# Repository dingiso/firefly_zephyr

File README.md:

# Firefly

# Software prerequisites
* Zephyr RTOS 3.4.0. See [Getting Started](https://docs.zephyrproject.org/latest/getting_started/index.html).
  When doing `west init`, use `west init zephyrproject --mr v3.4.0` to install this specific version.
  Make sure you can build some of Zephyr examples before proceeding.
* IDE: At the moment, Visual Studio Code with the bunch of plugins is used (VSCode will automatically ask to install them when
  opening this repository. Other IDEs can be also potentially used, more investigation is needed. Most of the commands are run
  from the command line anyway.
* Linux or running via WSL under Windows is recommended, as Black Magic Probe programming [doesn't work on Windows](https://github.com/zephyrproject-rtos/zephyr/issues/50789)
  When running under WSL, [usbipd](https://devblogs.microsoft.com/commandline/connecting-usb-devices-to-wsl/) can be used to allow interaction
  with the hardware from WSL.

# Hardware prerequisites
* For flashing, one of [nRF devkits](https://www.nordicsemi.com/Software-and-Tools/Development-Kits) is required.

# Building and flashing
To build of the images, mentioned below, use
```bash
west build <subfolder> --pristine
```
(`--pristine` can be omitted if previous build used same subfolder, it basically means "clean, non-incremental build")

To flash it, use
```bash
west flash
```

# Contents

This repo contains sources to build following firmware images:

## Firefly
This is the "main" image, located in the `firefly` folder.
Behaviours:
* Radio: will continously listen for the radio packets (see packet structure [here](common/magic_path_packet.h)).
  This is compatible with Locket firmware from [this branch](https://github.com/aeremin/Locket_fw/tree/7Colors) and
  with the Activator firmware described below. LED color will change according to packets received.
* Bluetooth: presents itself as connectable BLE device. Provides 2 BLE services:
  * Standard battery service, containing battery level (0-100) characteristic.
  * Custom service (UUID `8ec87060-8865-4eca-82e0-2ea8e45e8221`) exposing following characteristics:
    * "Beep" (UUID `8ec87062-8865-4eca-82e0-2ea8e45e8221`). Write-only characteristic, writing a byte to it will trigger short beep,
      byte written controls the volume.
    * "Blink" (UUID `8ec87063-8865-4eca-82e0-2ea8e45e8221`). Write-only characteristic, writing anything will trigger short series
      of blinks.

  Both of the services can be used by [dedicated Android app](https://install.appcenter.ms/users/a.eremin.msu/apps/ostranna-configurator/distribution_groups/public).
  App sources are [here](https://github.com/aeremin/ostranna_configurator).
* Battery measurement. Will continously monitor battery voltage and
  * Report it via bluetooth - see above.
  * Will disable radio and LED (will keep Bluetooth enabled) if battery level is low.

## Activator
This image can be used to trigger Firefly one or to provide some settings for it.
Behaviours:
* Radio: will continously transmit radio packets (see packet structure [here](common/magic_path_packet.h)).
* LED: will have a color corresponding to foreground color of packet being transmitted.
* Bluetooth: presents itself as connectable BLE device. Provides 2 BLE services:
  * Standard battery service, containing battery level (0-100) characteristic.
  * Custom service (UUID `8ec87060-8865-4eca-82e0-2ea8e45e8221`) exposing readable and writable characteristics corresponding to the
    fields of radio packet being transmitted. This allows to control the packet from e.g. phone.

  Both of the services can be used by [dedicated Android app](https://install.appcenter.ms/users/a.eremin.msu/apps/ostranna-configurator/distribution_groups/public).
  App sources are [here](https://github.com/aeremin/ostranna_configurator).

## Smoke test
This is a test image. Currently it only contains very basic test covering SPI usage and smooth LED transitions.
Will output the test log to the UART/RTT.

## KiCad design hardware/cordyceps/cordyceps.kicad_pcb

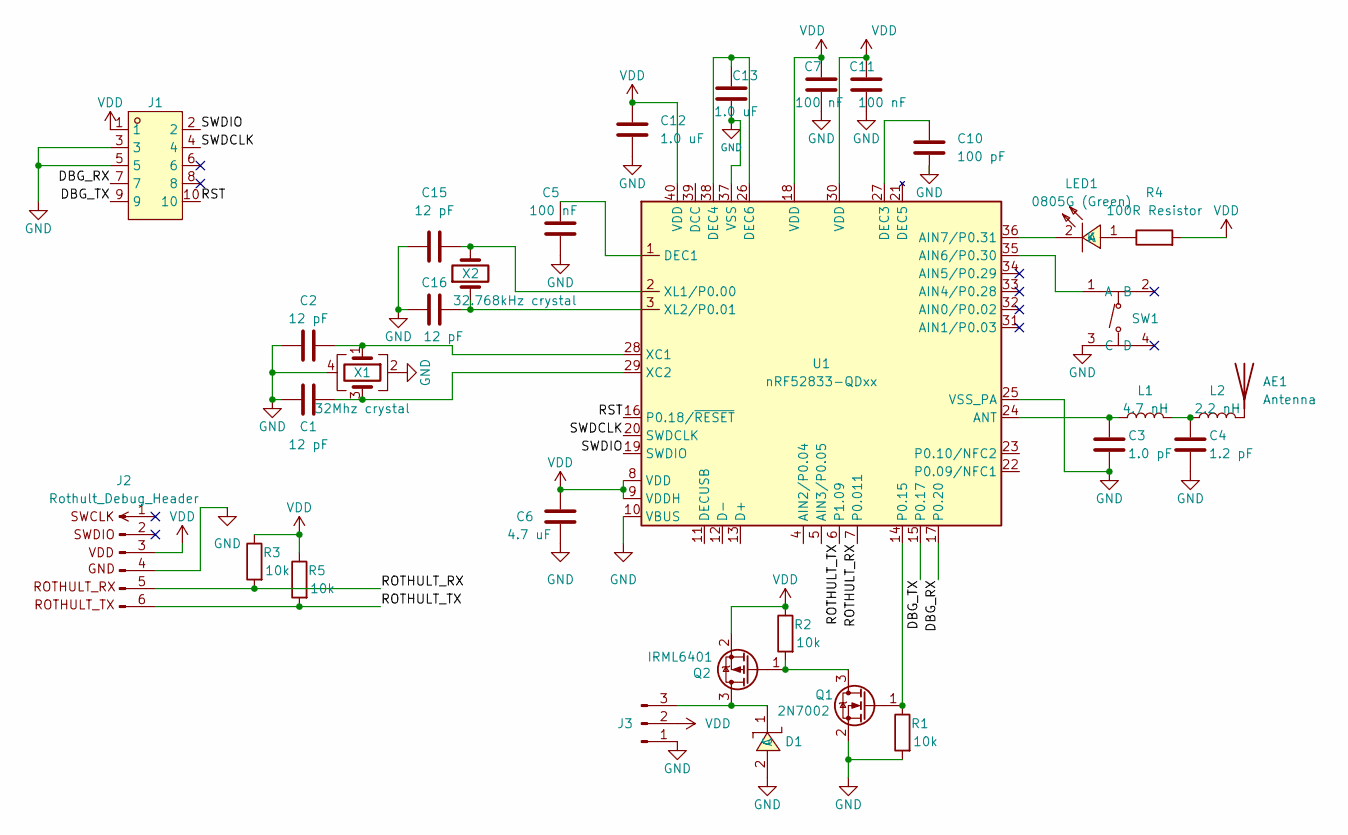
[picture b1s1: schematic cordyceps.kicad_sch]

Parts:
AE1: Antenna; Texas_SWRA117D_2.4GHz_Right
C1, C2, C15, C16: 12 pF; C_0402_1005Metric; LCSC C1547
C3: 1.0 pF; C_0402_1005Metric; LCSC C1550
C4: 1.2 pF; C_0603_1608Metric; LCSC C913539
C5, C7, C11: 100 nF; C_0402_1005Metric; LCSC C1525
C6: 4.7 uF; C_0603_1608Metric; LCSC C19666
C10: 100 pF; C_0402_1005Metric; LCSC C1546
C12, C13: 1.0 uF; C_0603_1608Metric; LCSC C15849
D1: 1N5819WS; SOD-323_L1.8-W1.3-LS2.5-RD; LCSC Part C191023
J1: KH-1.27PH180-2X5P-L7.2-SMT; HDR-SMD_10P-P1.27-V-M-R2-C5-LS5.5; LCSC Part C4943297
J2: Rothult_Debug_Header; PinHeader_1x06_P1.27mm_Vertical
J3: Conn_01x03_Pin; PinHeader_1x03_P2.54mm_Vertical
L1: 4.7 nH; L_0402_1005Metric; LCSC C2041409
L2: 2.2 nH; L_0402_1005Metric; LCSC C2044084
LED1: 0805G (Green); LED0805-R-RD; LCSC Part C2297
Q1: 2N7002; SOT-23; LCSC C8545
Q2: IRML6401; SOT-23; LCSC C3034
R1, R2, R3, R5: 10k; R_0402_1005Metric; LCSC C270371
R4: 100R Resistor; R_0603_1608Metric; LCSC C22775
SW1: TS-1187A-B-A-B; SW-SMD_4P-L5.1-W5.1-P3.70-LS6.5-TL-2; LCSC Part C318884
U1: nRF52833-QDxx; QFN-40-1EP_5x5mm_P0.4mm_EP3.6x3.6mm_ThermalVias; LCSC C2895249
X1: 32Mhz crystal; Crystal_SMD_2016-4Pin_2.0x1.6mm; LCSC C2901738
X2: 32.768kHz crystal; Crystal_SMD_3215-2Pin_3.2x1.5mm; LCSC C841881

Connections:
/DBG_RX: J1.7, U1.17 (P0.20)
/DBG_TX: J1.9, U1.15 (P0.17)
/ROTHULT_RX: J2.5 (ROTHULT_RX), R3.2, U1.7 (P0.011)
/ROTHULT_TX: J2.6 (ROTHULT_TX), R5.2, U1.6 (P1.09)
/RST: J1.10, U1.16 (P0.18/~RESET)
/SWDCLK: J1.4, U1.20 (SWDCLK)
/SWDIO: J1.2, U1.19 (SWDIO)
GND: C1.1, C2.1, C3.2, C4.2, C5.1, C6.2, C7.2, C10.2, C11.2, C12.2, C13.2, C15.1, C16.1, D1.2 (A), J1.3, J1.5, J2.4 (GND), J3.1, Q1.2 (S), R1.2, SW1.3 (C), U1.10 (VBUS), U1.25 (VSS_PA), U1.37 (VSS), X1.2, X1.4
unnamed: AE1.1 (A), L2.2
unnamed: C4.1, L1.2, L2.1
unnamed: D1.1 (C), J3.3, Q2.3 (D)
unnamed: LED1.1 (A), R4.1
unnamed: LED1.2 (K), U1.36 (AIN7/P0.31)
unnamed: Q1.3 (D), Q2.1 (G), R2.2
unnamed: Q1.1 (G), R1.1, U1.14 (P0.15)
unnamed: SW1.1 (A), U1.35 (AIN6/P0.30)
unnamed: C3.1, L1.1, U1.24 (ANT)
unnamed: C5.2, U1.1 (DEC1)
unnamed: C10.1, U1.27 (DEC3)
unnamed: C13.1, U1.26 (DEC6), U1.38 (DEC4)
unnamed: C2.2, U1.28 (XC1), X1.1
unnamed: C1.2, U1.29 (XC2), X1.3
unnamed: C15.2, U1.2 (XL1/P0.00), X2.2
unnamed: C16.2, U1.3 (XL2/P0.01), X2.1
VDD: C6.1, C7.1, C11.1, C12.1, J1.1, J2.3 (VDD), J3.2, Q2.2 (S), R2.1, R3.1, R4.2, R5.1, U1.8 (VDD), U1.9 (VDDH), U1.18 (VDD), U1.30 (VDD), U1.40 (VDD)

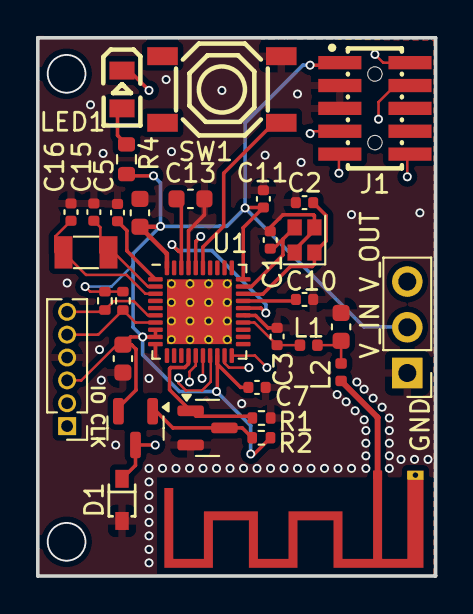
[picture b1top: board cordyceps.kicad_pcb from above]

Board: 4 copper layers, 22.1 x 29.9 mm, 32 parts (0 on the bottom side), 25 nets.

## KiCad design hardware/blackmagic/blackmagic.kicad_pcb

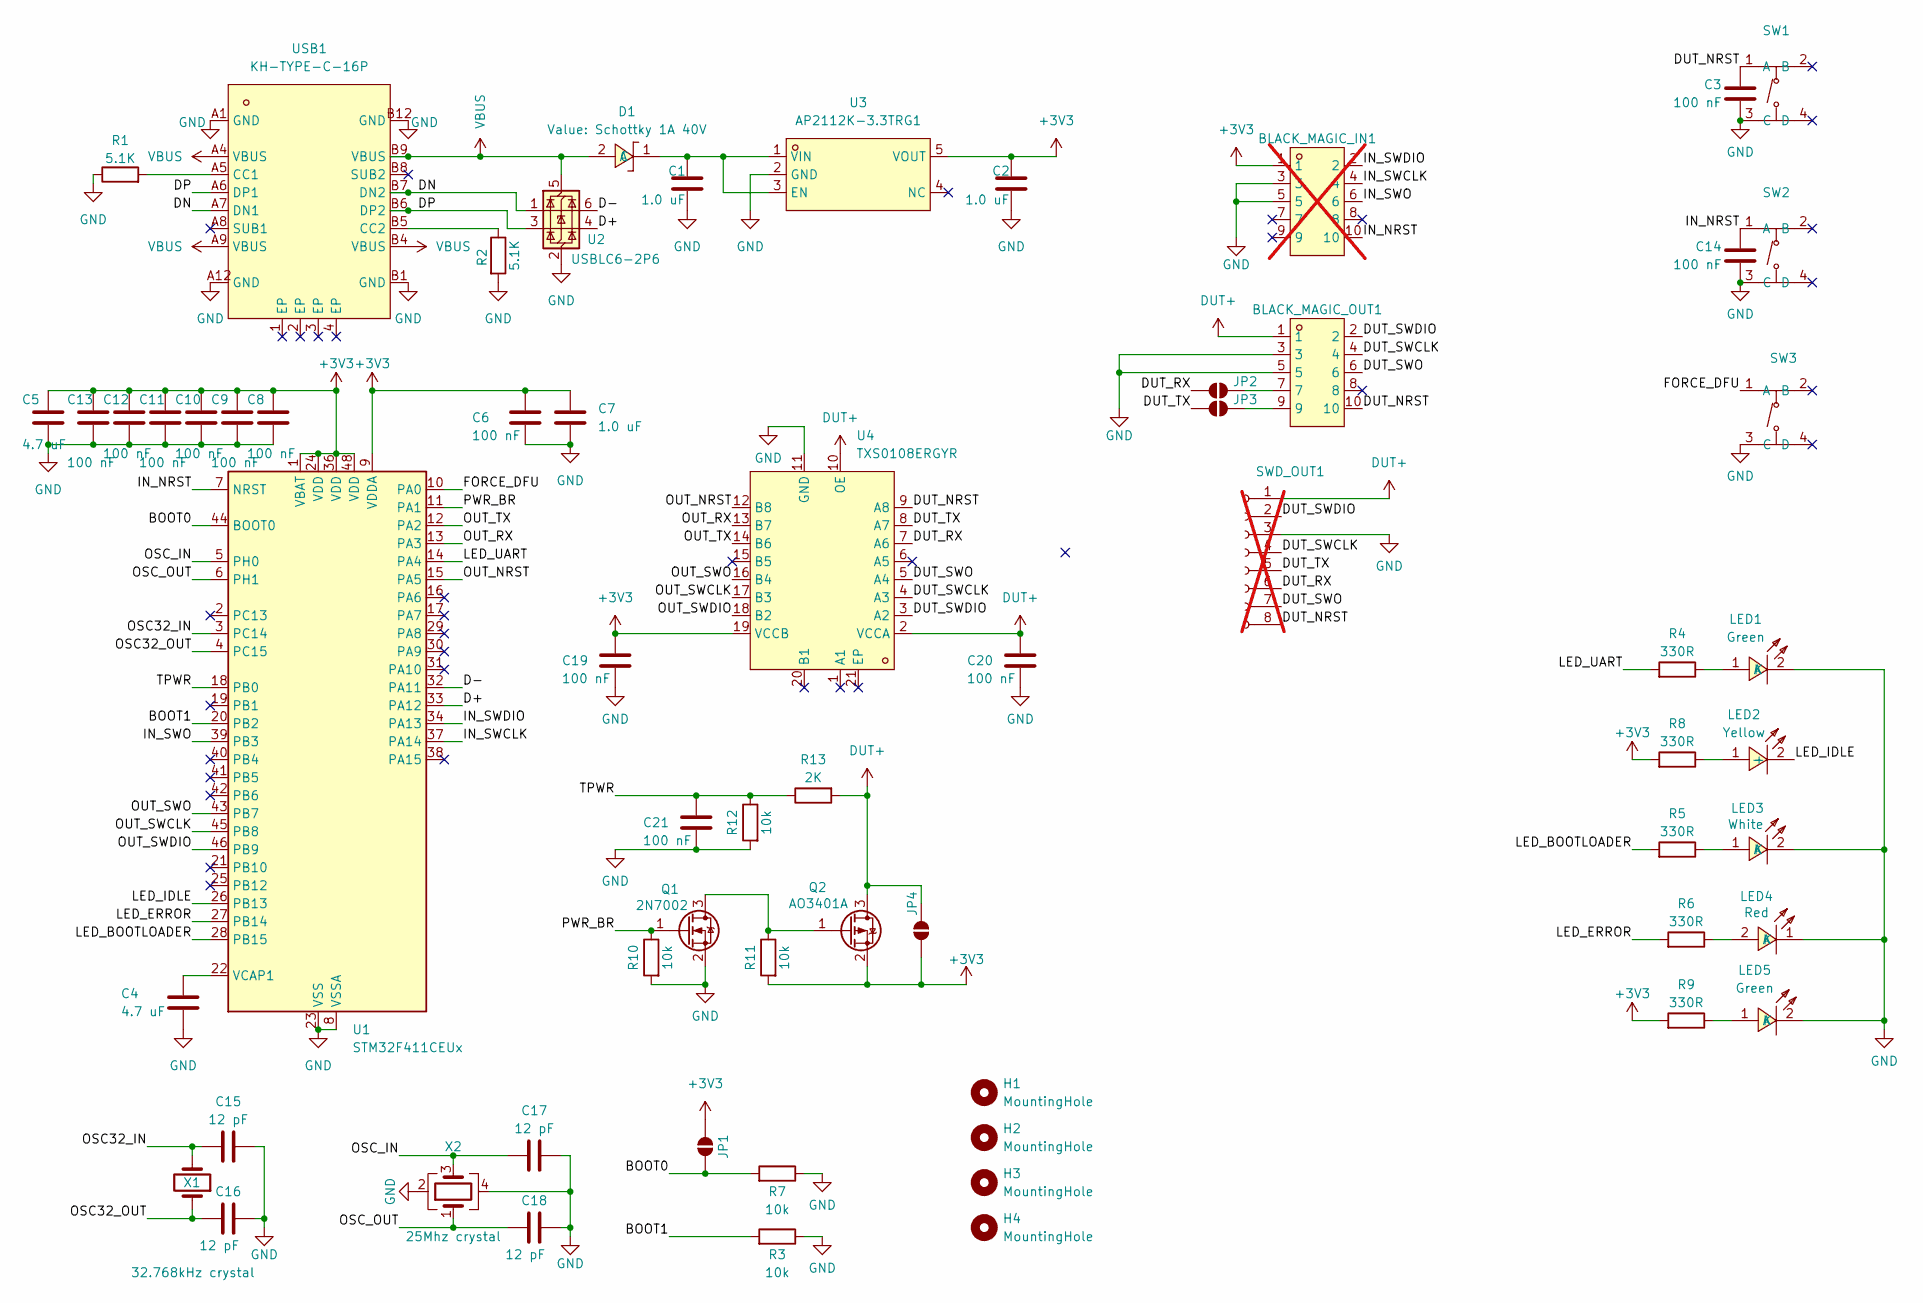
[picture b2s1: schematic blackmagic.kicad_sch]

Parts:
BLACK_MAGIC_IN1: KH-1.27PH180-2X5P-L7.2-SMT; HDR-SMD_10P-P1.27-V-M-R2-C5-LS5.5; LCSC Part C4943297; not fitted
BLACK_MAGIC_OUT1: KH-1.27PH180-2X5P-L7.2-SMT; HDR-SMD_10P-P1.27-V-M-R2-C5-LS5.5; LCSC Part C4943297
C1, C2, C7: 1.0 uF; C_0603_1608Metric; LCSC C15849
C3, C6, C8, C9, C10, C11, C12, C13, C14, C19, C20, C21: 100 nF; C_0402_1005Metric; LCSC C1525
C4, C5: 4.7 uF; C_0603_1608Metric; LCSC C19666
C15, C16, C17, C18: 12 pF; C_0402_1005Metric; LCSC C1547
D1: Schottky 1A 40V; SOD-323_L1.8-W1.3-LS2.5-RD; LCSC Part C191023
H1, H2, H3, H4: MountingHole; MountingHole_2.2mm_M2
JP1, JP2, JP3, JP4: SolderJumper_2_Open; SolderJumper-2_P1.3mm_Open_RoundedPad1.0x1.5mm
LED1, LED5: Green; LED0805-R-RD; LCSC Part C2297
LED2: Yellow; LED0805-R-RD; LCSC Part C2296
LED3: White; LED0603-R-RD_WHITE; LCSC Part C2290
LED4: Red; LED0603-RD; LCSC Part C2286
Q1: 2N7002; SOT-23; LCSC C8545
Q2: AO3401A; SOT-23; LCSC C15127
R1, R2: 5.1K; R_0402_1005Metric; LCSC Part C25941
R3, R7, R10, R11, R12: 10k; R_0402_1005Metric; LCSC C25744
R4, R5, R6, R8, R9: 330R; R_0603_1608Metric; LCSC C22775
R13: 2K; R_0402_1005Metric; LCSC C4109
SW1, SW2, SW3: TS-1187A-B-A-B; SW-SMD_4P-L5.1-W5.1-P3.70-LS6.5-TL-2; LCSC Part C318884
SWD_OUT1: Conn_01x08_Female; PinSocket_2x04_P2.54mm_Vertical; not fitted
U1: STM32F411CEUx; UFQFPN-48_L7.0-W7.0-P0.50-BL-EP; LCSC C60420
U2: USBLC6-2P6; SOT-666-6_L1.6-W1.2-P0.50-LS1.6-BR; LCSC C15999
U3: AP2112K-3.3TRG1; SOT-25-5_L2.9-W1.6-P0.95-LS2.8-BL; LCSC Part C51118
U4: TXS0108ERGYR; VQFN-20_L4.6-W3.6-P0.50-BL-EP; LCSC Part C90706
USB1: KH-TYPE-C-16P; USB-C-SMD_KH-TYPE-C-16P; LCSC Part C709357
X1: 32.768kHz crystal; Crystal_SMD_3215-2Pin_3.2x1.5mm; LCSC C841881
X2: 25Mhz crystal; Crystal_SMD_2016-4Pin_2.0x1.6mm; LCSC C5265839

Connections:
+3V3: BLACK_MAGIC_IN1.1, C2.1, C5.1, C6.1, C7.1, C8.1, C9.1, C10.1, C11.1, C12.1, C13.1, C19.1, JP1.2 (B), JP4.2 (B), Q2.2 (S), R8.2, R9.2, R11.1, U1.1 (VBAT), U1.9 (VDDA), U1.24 (VDD), U1.36 (VDD), U1.48 (VDD), U3.5 (VOUT), U4.19 (VCCB)
/BOOT0: JP1.1 (A), R7.1, U1.44 (BOOT0)
/BOOT1: R3.1, U1.20 (PB2)
/D+: U1.33 (PA12), U2.4 (I/O2)
/D-: U1.32 (PA11), U2.6 (I/O1)
/DN: U2.1 (I/O1), USB1.A7 (DN1), USB1.B7 (DN2)
/DP: U2.3 (I/O2), USB1.A6 (DP1), USB1.B6 (DP2)
/DUT_NRST: BLACK_MAGIC_OUT1.10, C3.1, SW1.1 (A), SWD_OUT1.8, U4.9 (A8)
/DUT_RX: JP2.2 (B), SWD_OUT1.6, U4.7 (A6)
/DUT_SWCLK: BLACK_MAGIC_OUT1.4, SWD_OUT1.4, U4.4 (A3)
/DUT_SWDIO: BLACK_MAGIC_OUT1.2, SWD_OUT1.2, U4.3 (A2)
/DUT_SWO: BLACK_MAGIC_OUT1.6, SWD_OUT1.7, U4.5 (A4)
/DUT_TX: JP3.2 (B), SWD_OUT1.5, U4.8 (A7)
/FORCE_DFU: SW3.1 (A), U1.10 (PA0)
/IN_NRST: BLACK_MAGIC_IN1.10, C14.1, SW2.1 (A), U1.7 (NRST)
/IN_SWCLK: BLACK_MAGIC_IN1.4, U1.37 (PA14)
/IN_SWDIO: BLACK_MAGIC_IN1.2, U1.34 (PA13)
/IN_SWO: BLACK_MAGIC_IN1.6, U1.39 (PB3)
/LED_BOOTLOADER: R5.2, U1.28 (PB15)
/LED_ERROR: R6.2, U1.27 (PB14)
/LED_IDLE: LED2.2 (-), U1.26 (PB13)
/LED_UART: R4.2, U1.14 (PA4)
/OSC32_IN: C15.2, U1.3 (PC14), X1.2
/OSC32_OUT: C16.2, U1.4 (PC15), X1.1
/OSC_IN: C17.2, U1.5 (PH0), X2.3
/OSC_OUT: C18.2, U1.6 (PH1), X2.1
/OUT_NRST: U1.15 (PA5), U4.12 (B8)
/OUT_RX: U1.13 (PA3), U4.13 (B7)
/OUT_SWCLK: U1.45 (PB8), U4.17 (B3)
/OUT_SWDIO: U1.46 (PB9), U4.18 (B2)
/OUT_SWO: U1.43 (PB7), U4.16 (B4)
/OUT_TX: U1.12 (PA2), U4.14 (B6)
/PWR_BR: Q1.1 (G), R10.2, U1.11 (PA1)
/TPWR: C21.1, R12.2, R13.2, U1.18 (PB0)
DUT+: BLACK_MAGIC_OUT1.1, C20.1, JP4.1 (A), Q2.3 (D), R13.1, SWD_OUT1.1, U4.2 (VCCA), U4.10 (OE)
GND: BLACK_MAGIC_IN1.3, BLACK_MAGIC_IN1.5, BLACK_MAGIC_OUT1.3, BLACK_MAGIC_OUT1.5, C1.2, C2.2, C3.2, C4.2, C5.2, C6.2, C7.2, C8.2, C9.2, C10.2, C11.2, C12.2, C13.2, C14.2, C15.1, C16.1, C17.1, C18.1, C19.2, C20.2, C21.2, LED1.2 (K), LED3.2 (K), LED4.1 (K), LED5.2 (K), Q1.2 (S), R1.1, R2.2, R3.2, R7.2, R10.1, R12.1, SW1.3 (C), SW2.3 (C), SW3.3 (C), SWD_OUT1.3, U1.8 (VSSA), U1.23 (VSS), U1.35 (VSS), U1.47 (VSS), U1.49 (VSS), U2.2 (GND), U3.2 (GND), U4.11 (GND), USB1.A1 (GND), USB1.A12 (GND), USB1.B1 (GND), USB1.B12 (GND), X2.2, X2.4
unnamed: C1.1, D1.1 (C), U3.1 (VIN), U3.3 (EN)
unnamed: BLACK_MAGIC_OUT1.7, JP2.1 (A)
unnamed: BLACK_MAGIC_OUT1.9, JP3.1 (A)
unnamed: LED1.1 (A), R4.1
unnamed: LED2.1 (+), R8.1
unnamed: LED3.1 (A), R5.1
unnamed: LED4.2 (A), R6.1
unnamed: LED5.1 (A), R9.1
unnamed: Q1.3 (D), Q2.1 (G), R11.2
unnamed: C4.1, U1.22 (VCAP1)
unnamed: R1.2, USB1.A5 (CC1)
unnamed: R2.1, USB1.B5 (CC2)
VBUS: D1.2 (A), U2.5 (VBUS), USB1.A4 (VBUS), USB1.A9 (VBUS), USB1.B4 (VBUS), USB1.B9 (VBUS)

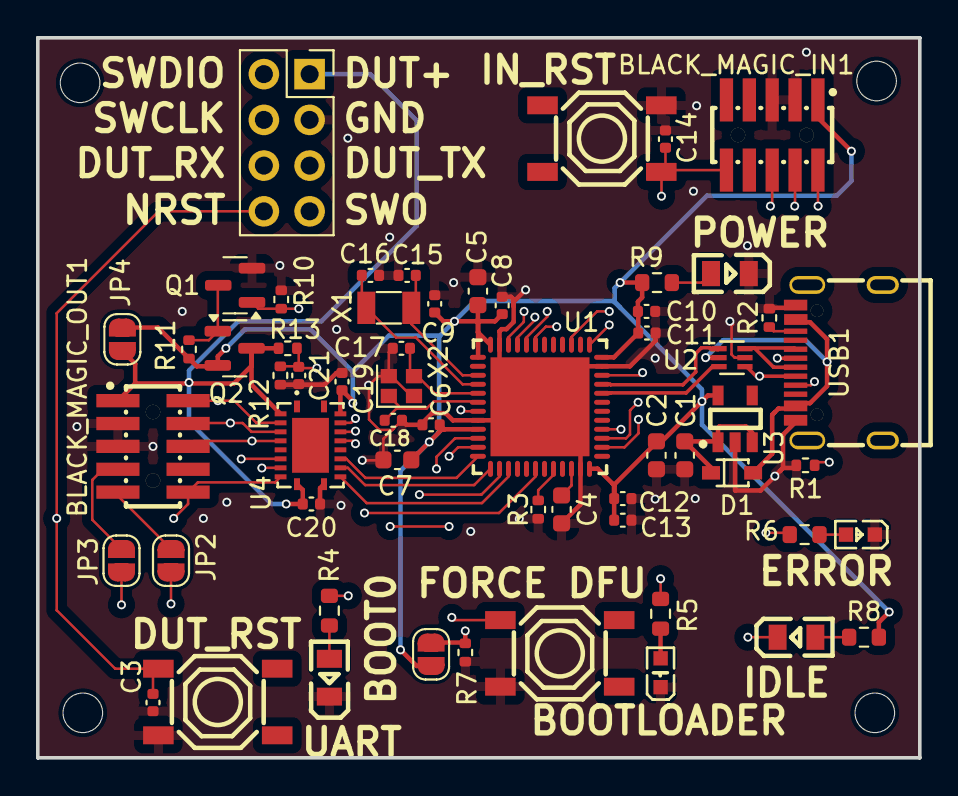
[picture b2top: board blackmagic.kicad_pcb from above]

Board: 4 copper layers, 49.0 x 40.0 mm, 63 parts (0 on the bottom side), 49 nets.

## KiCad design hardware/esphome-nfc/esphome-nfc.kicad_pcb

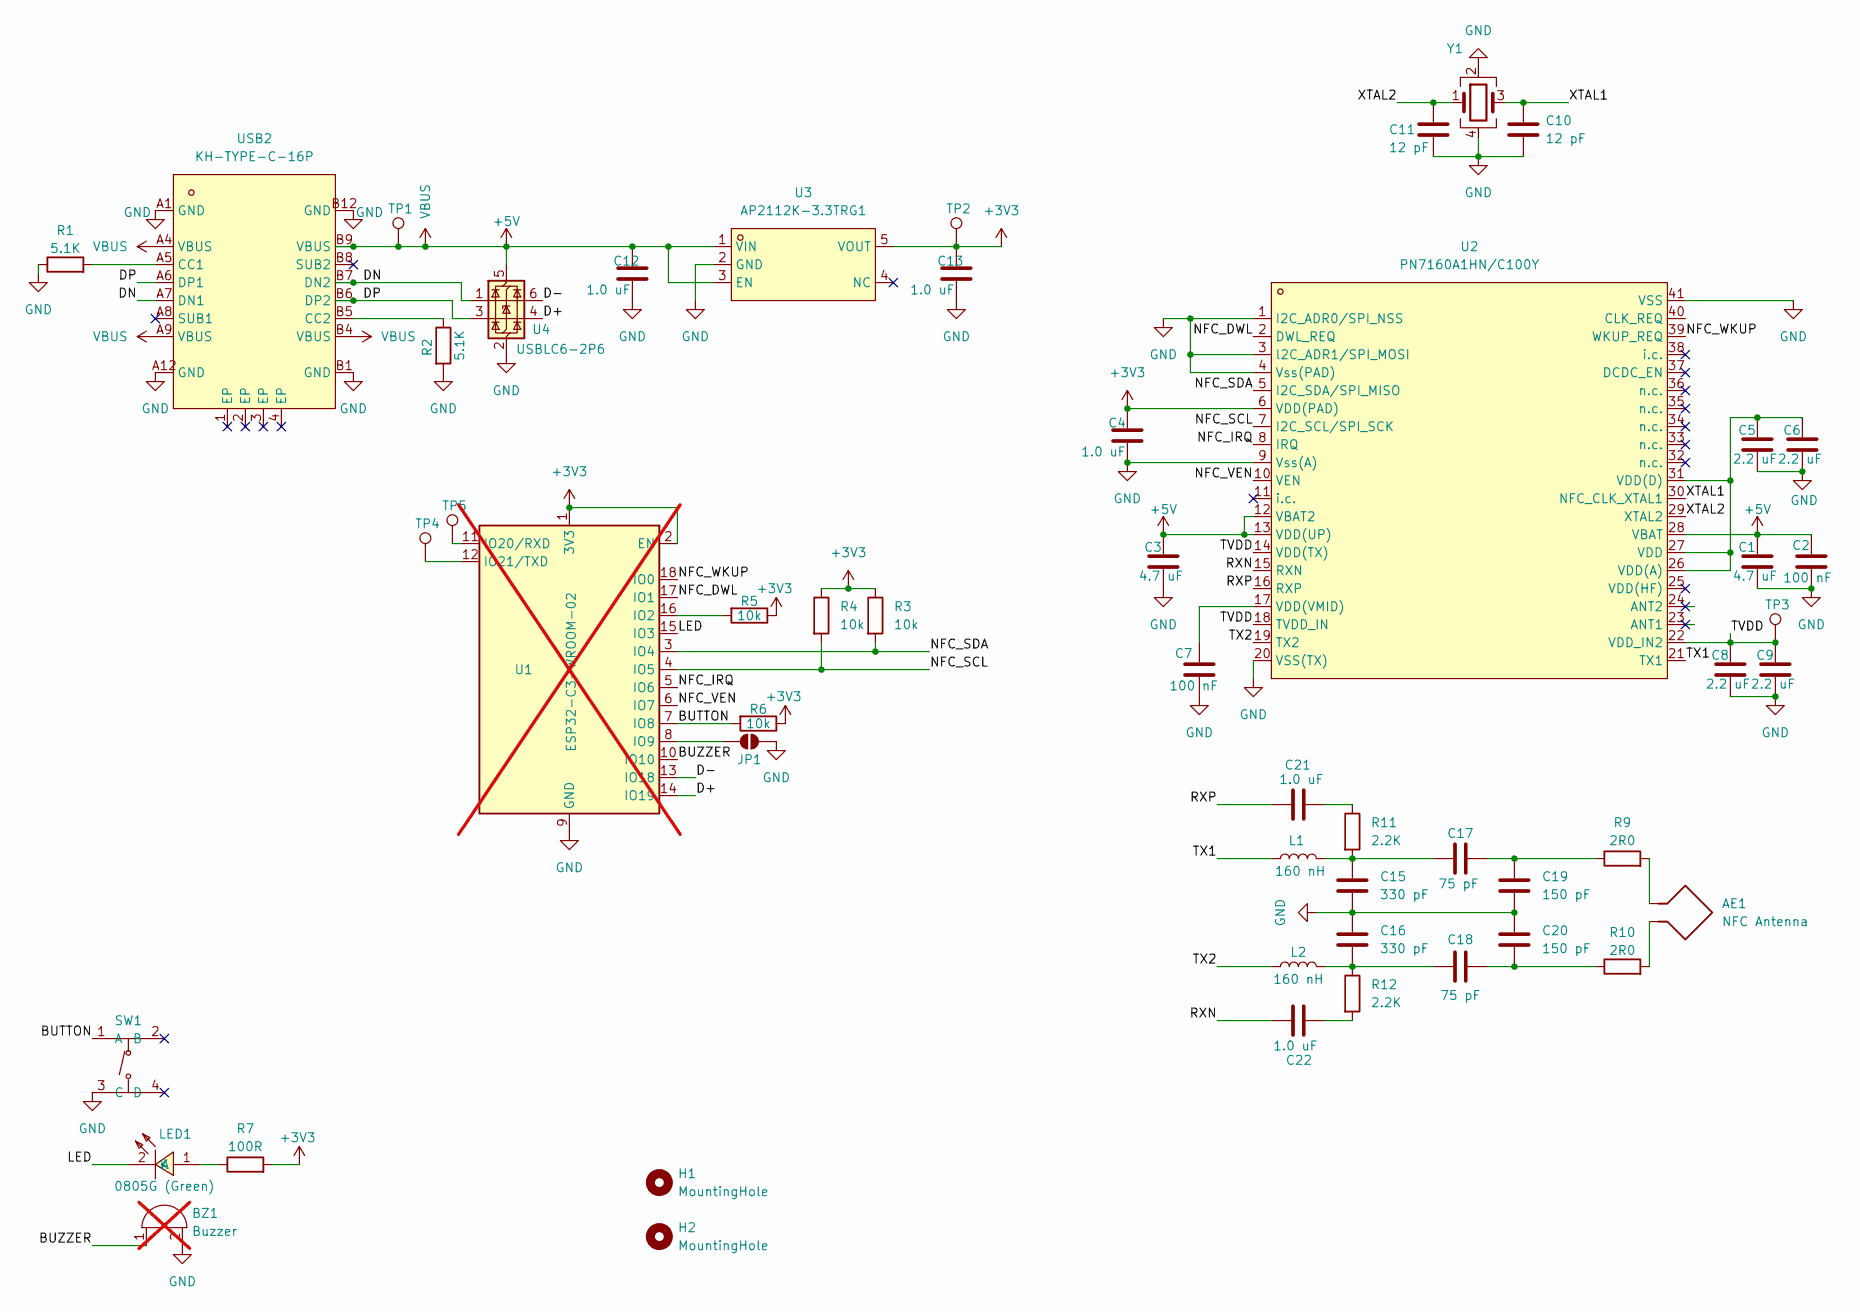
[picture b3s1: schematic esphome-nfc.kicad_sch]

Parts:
AE1: NFC Antenna
BZ1: Buzzer; Buzzer_12x9.5RM7.6; not fitted
C1, C3: 4.7 uF; C_0603_1608Metric; LCSC C19666
C2, C7: 100 nF; C_0402_1005Metric; LCSC C1525
C4, C12, C13, C21, C22: 1.0 uF; C_0603_1608Metric; LCSC C15849
C5, C6, C8, C9: 2.2 uF; C_0603_1608Metric; LCSC C23630
C10, C11: 12 pF; C_0402_1005Metric; LCSC C1547
C15, C16: 330 pF; C_0603_1608Metric; LCSC C1664
C17, C18: 75 pF; C_0402_1005Metric; LCSC C107010
C19, C20: 150 pF; C_0603_1608Metric; LCSC C1594
H1, H2: MountingHole; MountingHole_2.7mm_M2.5
JP1: SolderJumper_2_Open; SolderJumper-2_P1.3mm_Open_RoundedPad1.0x1.5mm
L1, L2: 160 nH; L_0603_1608Metric; LCSC C437367
LED1: 0805G (Green); LED0805-R-RD; LCSC Part C2297
R1, R2: 5.1K; R_0402_1005Metric; LCSC Part C25941
R3, R4, R5, R6: 10k; R_0402_1005Metric; LCSC C25744
R7: 100R; R_0603_1608Metric; LCSC C22775
R9, R10: 2R0; R_1206_3216Metric; LCSC C17942
R11, R12: 2.2K; R_0603_1608Metric; LCSC C278639
SW1: TS-1187A-B-A-B; SW-SMD_4P-L5.1-W5.1-P3.70-LS6.5-TL-2; LCSC Part C318884
TP1, TP2, TP3, TP4, TP5: TestPoint_Pad_D1.0mm
U1: ESP32-C3-WROOM-02; not fitted
U2: PN7160A1HN/C100Y; HVQFN-40_L6.0-W6.0-P0.50-BL-EP4.1; LCSC Part C3303790
U3: AP2112K-3.3TRG1; SOT-25-5_L2.9-W1.6-P0.95-LS2.8-BL; LCSC Part C51118
U4: USBLC6-2P6; SOT-666-6_L1.6-W1.2-P0.50-LS1.6-BR; LCSC C15999
USB2: KH-TYPE-C-16P; USB-C-SMD_KH-TYPE-C-16P; LCSC Part C709357
Y1: Crystal_GND24; Crystal_SMD_2016-4Pin_2.0x1.6mm; LCSC Part C338245

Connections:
+3V3: C4.1, C13.1, R3.1, R4.1, R5.1, R6.1, R7.2, TP2.1, U1.1 (3V3), U1.2 (EN), U2.6 (VDD(PAD)), U3.5 (VOUT)
+5V: C1.1, C2.1, C3.1, C12.1, TP1.1, U2.12 (VBAT2), U2.13 (VDD(UP)), U2.28 (VBAT), U3.1 (VIN), U3.3 (EN), U4.5 (VBUS), USB2.A4 (VBUS), USB2.A9 (VBUS), USB2.B4 (VBUS), USB2.B9 (VBUS)
/BUTTON: R6.2, SW1.1 (A), U1.7 (IO8)
/BUZZER: BZ1.1 (+), U1.10 (IO10)
/D+: U1.14 (IO19), U4.4 (I/O2)
/D-: U1.13 (IO18), U4.6 (I/O1)
/DN: U4.1 (I/O1), USB2.A7 (DN1), USB2.B7 (DN2)
/DP: U4.3 (I/O2), USB2.A6 (DP1), USB2.B6 (DP2)
/LED: LED1.2 (K), U1.15 (IO3)
/NFC_DWL: U1.17 (IO1), U2.2 (DWL_REQ)
/NFC_IRQ: U1.5 (IO6), U2.8 (IRQ)
/NFC_SCL: R4.2, U1.4 (IO5), U2.7 (I2C_SCL/SPI_SCK)
/NFC_SDA: R3.2, U1.3 (IO4), U2.5 (I2C_SDA/SPI_MISO)
/NFC_VEN: U1.6 (IO7), U2.10 (VEN)
/NFC_WKUP: U1.18 (IO0), U2.39 (WKUP_REQ)
/RXN: C22.1, U2.15 (RXN)
/RXP: C21.2, U2.16 (RXP)
/TVDD: C8.1, C9.1, TP3.1, U2.14 (VDD(TX)), U2.18 (TVDD_IN), U2.22 (VDD_IN2)
/TX1: L1.1, U2.21 (TX1)
/TX2: L2.1, U2.19 (TX2)
/XTAL1: C10.1, U2.30 (NFC_CLK_XTAL1), Y1.3
/XTAL2: C11.1, U2.29 (XTAL2), Y1.1
GND: BZ1.2 (-), C1.2, C2.2, C3.2, C4.2, C5.2, C6.2, C7.2, C8.2, C9.2, C10.2, C11.2, C12.2, C13.2, C15.2, C16.1, C19.2, C20.1, JP1.2 (B), R1.1, R2.2, SW1.3 (C), U1.9 (GND), U1.19 (GND), U2.1 (I2C_ADR0/SPI_NSS), U2.3 (l2C_ADR1/SPI_MOSI), U2.4 (Vss(PAD)), U2.9 (Vss(A)), U2.20 (VSS(TX)), U2.41 (VSS), U3.2 (GND), U4.2 (GND), USB2.A1 (GND), USB2.A12 (GND), USB2.B1 (GND), USB2.B12 (GND), Y1.2, Y1.4
unnamed: C15.1, C17.1, L1.2, R11.2
unnamed: C16.2, C18.1, L2.2, R12.1
unnamed: C17.2, C19.1, R9.1
unnamed: C18.2, C20.2, R10.1
unnamed: C21.1, R11.1
unnamed: C22.2, R12.2
unnamed: JP1.1 (A), U1.8 (IO9)
unnamed: LED1.1 (A), R7.1
unnamed: AE1.1, R9.2
unnamed: AE1.2, R10.2
unnamed: R5.2, U1.16 (IO2)
unnamed: TP5.1, U1.11 (IO20/RXD)
unnamed: TP4.1, U1.12 (IO21/TXD)
unnamed: C5.1, C6.1, U2.26 (VDD(A)), U2.27 (VDD), U2.31 (VDD(D))
unnamed: C7.1, U2.17 (VDD(VMID))
unnamed: R1.2, USB2.A5 (CC1)
unnamed: R2.1, USB2.B5 (CC2)

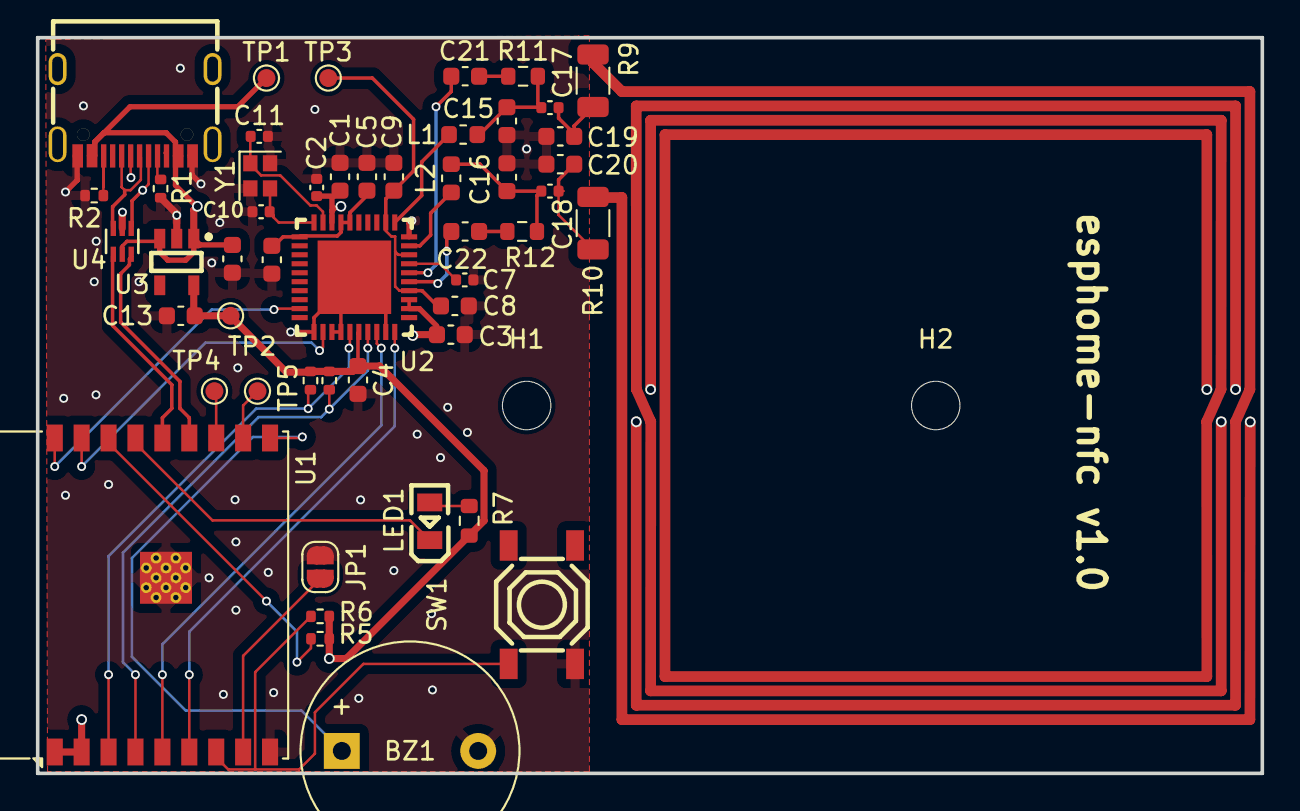
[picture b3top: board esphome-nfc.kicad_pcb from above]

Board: 4 copper layers, 68.2 x 41.0 mm, 51 parts (0 on the bottom side), 38 nets.

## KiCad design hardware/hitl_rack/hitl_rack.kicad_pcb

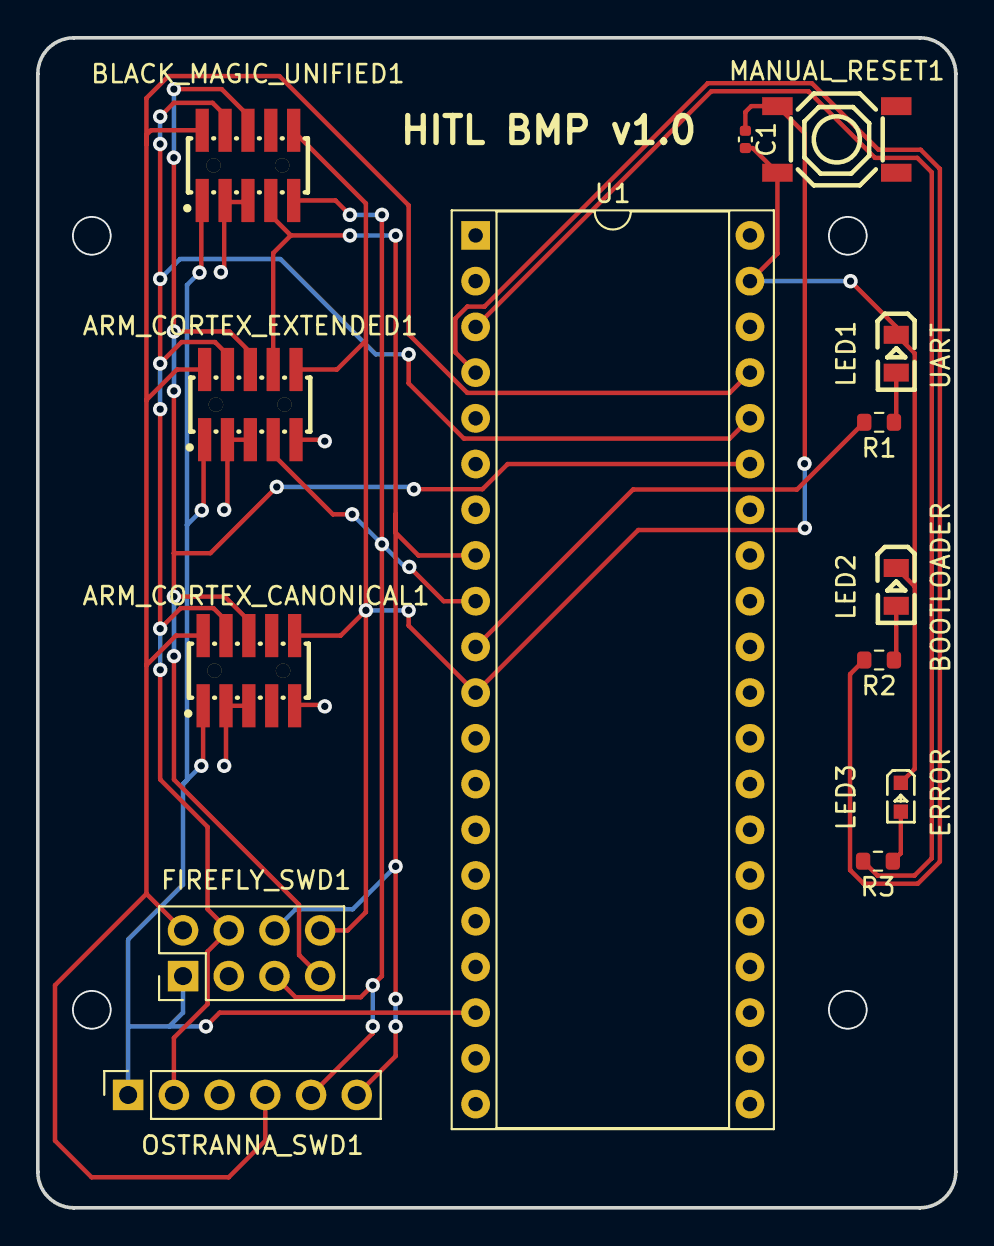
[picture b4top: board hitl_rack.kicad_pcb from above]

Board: 2 copper layers, 51.0 x 65.0 mm, 14 parts (0 on the bottom side), 14 nets.

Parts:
ARM_CORTEX_CANONICAL1: KH-1.27PH180-2X5P-L7.2-SMT; HDR-SMD_10P-P1.27-V-M-R2-C5-LS5.5
ARM_CORTEX_EXTENDED1: KH-1.27PH180-2X5P-L7.2-SMT; HDR-SMD_10P-P1.27-V-M-R2-C5-LS5.5
BLACK_MAGIC_UNIFIED1: KH-1.27PH180-2X5P-L7.2-SMT; HDR-SMD_10P-P1.27-V-M-R2-C5-LS5.5
C1: 100 nF; C_0402_1005Metric
FIREFLY_SWD1: Conn_01x08_Female; PinSocket_2x04_P2.54mm_Vertical
LED1: 0805G (Green); LED0805-R-RD
LED2: 17-21SUYC/TR8; LED0805-R-RD
LED3: KT-0603R; LED0603-RD
MANUAL_RESET1: TS-1187A-B-A-B; SW-SMD_4P-L5.1-W5.1-P3.70-LS6.5-TL-2
OSTRANNA_SWD1: Conn_01x06_Socket; PinSocket_1x06_P2.54mm_Vertical
R1, R2, R3: 330R; R_0603_1608Metric
U1: BlackPill; DIP-40_W15.24mm_Socket

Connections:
/DUT_RX: ARM_CORTEX_EXTENDED1.8, BLACK_MAGIC_UNIFIED1.7, FIREFLY_SWD1.6, OSTRANNA_SWD1.6, U1.8 (A2)
/DUT_TX: ARM_CORTEX_EXTENDED1.7, BLACK_MAGIC_UNIFIED1.9, FIREFLY_SWD1.5, OSTRANNA_SWD1.5, U1.9 (A3)
/LED_BOOTLOADER: R2.2, U1.4 (C15)
/LED_ERROR: R3.2, U1.3 (C14)
/LED_UART: R1.2, U1.10 (A4)
/NRST: ARM_CORTEX_CANONICAL1.10, ARM_CORTEX_EXTENDED1.10, BLACK_MAGIC_UNIFIED1.10, C1.1, FIREFLY_SWD1.8, MANUAL_RESET1.1 (A), U1.11 (A5)
/SWCLK: ARM_CORTEX_CANONICAL1.4, ARM_CORTEX_EXTENDED1.4, BLACK_MAGIC_UNIFIED1.4, FIREFLY_SWD1.4, OSTRANNA_SWD1.2, U1.36 (B8)
/SWDIO: ARM_CORTEX_CANONICAL1.2, ARM_CORTEX_EXTENDED1.2, BLACK_MAGIC_UNIFIED1.2, FIREFLY_SWD1.2, OSTRANNA_SWD1.4, U1.37 (B9)
/SWO: ARM_CORTEX_CANONICAL1.6, ARM_CORTEX_EXTENDED1.6, BLACK_MAGIC_UNIFIED1.6, FIREFLY_SWD1.7, U1.35 (B7)
/TRGT+: ARM_CORTEX_CANONICAL1.1, ARM_CORTEX_EXTENDED1.1, BLACK_MAGIC_UNIFIED1.1, FIREFLY_SWD1.1, OSTRANNA_SWD1.1, U1.18 (3.3ii)
GND: ARM_CORTEX_CANONICAL1.3, ARM_CORTEX_CANONICAL1.5, ARM_CORTEX_CANONICAL1.9, ARM_CORTEX_EXTENDED1.3, ARM_CORTEX_EXTENDED1.5, ARM_CORTEX_EXTENDED1.9, BLACK_MAGIC_UNIFIED1.3, BLACK_MAGIC_UNIFIED1.5, C1.2, FIREFLY_SWD1.3, LED1.2 (K), LED2.2 (-), LED3.1 (K), MANUAL_RESET1.3 (C), OSTRANNA_SWD1.3, U1.39 (GNDi)
unnamed: LED1.1 (A), R1.1
unnamed: LED2.1 (+), R2.1
unnamed: LED3.2 (A), R3.1

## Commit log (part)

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2020-02-13 Hello world Zephyr RTOS app
2020-02-14 Add radio TX support
2020-02-15 Fix SPI frequency value
2020-02-15 Add missing wait for gdo0
2020-02-18 Remove led functionality for now
2020-02-19 Implement basic LED support
2020-02-20 Increase PWM frequency to reduce flickering
2020-02-22 Allow to safely destruct RgbLed
2020-02-23 Remove unused variable
2020-02-23 Improve debug logging in CC1101 code and add a link to the datasheet
2020-02-23 Use radio settings from https://github.com/Kreyl/Locket_fw/blob/7Colors/Radio/cc1101_rf_settings.h
2020-02-23 Fix some issues with battery management and provide a comment about some hacks/problems
2020-02-25 Extract libraries to the separate folder
2020-02-25 Clean up devicetree and kconfigs
    Remove stuff we don't have, set proper pins for pill/eeprom I2Cs, etc
2020-02-26 Basic BLE functionality (advertising + battery data reporting)
2020-02-27 Enable LED power stabilizer
2020-02-28 Fix build script
2020-02-28 Report battery state of Activator
2020-02-28 Add missing mutex locks
2020-02-28 Move BT_GATT_ATTRIBUTE fix to common file
2020-02-28 Transmit configured radio packet
2020-02-29 Add move assignment for Timer
2020-02-29 Fix UUID comments
2020-03-01 Allow to set volume level for beep
2020-03-01 Use Color in MagicPathRadioPacket directly
2020-03-01 Low-power mode
2020-03-01 Put buzzer on separate PWM - it needs to have different frequency
2020-03-01 Implement blinking
2020-03-06 Remove BT_GATT_ATTRIBUTE re-definition
    Not needed after https://github.com/zephyrproject-rtos/zephyr/pull/23167 was merged in
2020-03-06 Create dummy on-hardware unit test
2020-03-06 Add a bit more CC1101 unit tests
2020-03-07 Update battery level calculation function
2020-03-07 Use explicit lambda captures for the better understanding of their size
2020-03-07 Don't depend on bluetooth in the test
2020-03-07 Use _proper_ aliased device name for better portability
    This is the fix for 32615ac35939b2e4b5c36ac17cbb7426173709c4.
2020-03-08 Add Timer test
2020-03-09 Add missing timer --> kernel dependency
2020-03-12 Use EEPROM instead of flash
2020-03-12 Add missing #pragma once
2020-03-12 Fix activator not sending proper radio packet
2020-03-15 Don't use nrfjprog for flashing - it tries to change protocol from SWD to JTAG and back...
    which is annoying if e.g. RTT logger is already running
2020-03-15 Set up automatic releases on tags
2020-03-19 Re-add flash definition to devicetree
2020-03-20 Download build artifact
2020-03-20 Check for test success
2020-03-28 Basic sequencing support
2020-12-28 Dummy commit to trigger CI
2021-01-03 Bump zephyr version a bit
2021-01-03 Fix whitespace in readme
2021-01-03 Enable daily builds
2021-01-04 Use K_MSEC macro
2021-01-05 Migrate to Zephyr RTOS 2.4.0
2021-06-24 Never return from test main() function
2021-06-24 Remove empty unused file
2021-06-25 Upgrade to Zephyr RTOS 2.6.0
    For some reason, starting with 2.5.0 eeprom writes in largish addresses consistently fail. For now change test to only use 1kb.
2021-07-04 Support locket board. smoke_test passes.
2022-08-10 Migrate to Zephyr RTOS 3.1.0
2022-08-11 Emit short beep on successful test and long on failure
2022-08-12 Extract PrintkEventHandler to a separate library
2022-08-14 Switch to using nRF VC Code extensions for Zephyr RTOS
2022-08-14 Migrate to newer pwm_set functions from deprecated ones
2022-09-11 Enable real-device testing on self-hosted runner
2022-09-11 Fix file path
2022-09-15 Run daily CI during the day instead of night
2022-09-30 Remove all flashing runners except blackmagicprobe
2022-10-01 Support Zephyr 3.2
    For some reason, UART logging is not working at the moment
2022-10-04 Add NRF plugin config
2022-10-16 Use Zephyr 3.2.0 instead of 3.2.0-rc3
2023-01-10 Switch back to using pigweed from head
2023-02-24 Revert back to Zephyr RTOS 3.2.0 - smoke test fails to build on 3.3.0
    https://github.com/aeremin/firefly_zephyr/commit/b6d4233a9de1750cb7c3ba632ff16c649fa6ed7a
2023-03-15 Remove unneeded CMake override
2023-03-16 Add a proto usage example
    Tricky parts: for proto generation to work, we need to activate pigweed environment (run pigweed.bat). Then we need to run all west commands in that environment (and NRF extension doesn't do this, so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
2023-03-17 Reduce the number of API-installed dependencies
    They are provided by Pigweed now
2023-03-17 Stop CMake Tools extensions trying to auto-run configure on every CMakeLists.txt edit
2023-03-18 Temporarily force the location of compile_commands.json
    Argh, not sure how to make it work properly with **all** folders.
2023-03-18 Add a final to help compiler optimise virtual calls away
2023-03-18 Use EXCLUDE_FROM_ALL when adding subdirectories
    It seems that Zephyr tries to build `all` target no matter what we actually depend on.
    But e.g. some targets in common require that specific peripheral is defined.
    With EXCLUDE_FROM_ALL only explicit dependencies are linked to the final image.
    So we can remove those `if(CONFIG_ADC) ...` in common/CMakeLists.txt.
2023-03-18 Use pw::Function instead of std::function
2023-03-19 First version of MFRC522 driver
    Can wakeup tags and detect their presence (no meaningful interactions like getting UIDs or reading/writing data yet)
2023-03-19 Enable pw bloat reports for lock_test
2023-03-20 Start working on AntiColl PICC command sending
    For now we only do a first cascade
2023-03-21 Clean up the code a bit - make Nfc a (mostly) proper class
2023-03-24 Reformat the devicetree
2023-03-24 Configure and try keyboard
2023-03-24 Configure and test PWM devices (leds, buzzer)
2023-03-24 Configure and test EEPROM
    Tricky part was address-width (16 instead of 8 in firefly)
2023-03-25 Move RPC-related stuff into common folder
    Clean up lock_test functionality - leave only unit-tests and RPC.
2023-03-26 Run more tests on lock_v01
2023-03-27 Add beep on test success
2023-03-29 Add support for blackmagicprobe to lock board
    Also start add small documentation file
2023-03-29 Disable unused random generator module
2023-03-29 Move keyboard devicetree node to an overlay
2023-03-29 Fix the board definition - UART RX was broken **facepalm**
2023-03-31 Write a nice onboarding doc
    to make a future-me happy and proud.
2023-04-01 Add a TODO doc explaining why RPC logging is still problematic
2023-04-01 Use Nordic's version of Zephyr RTOS
2023-04-02 Fix vscode settings file
2023-04-03 Fix some build issues
2023-05-12 Switch back to mainstream pigweed
2023-05-19 Start working on generic spi device and st25r3911b driver
2023-05-20 Fix register address structure being partially uninitialized in some cases
2023-05-20 Add IoConfigurationRegister1 definition for st25r3911b
2023-05-21 Add st25r3911b command list
2023-05-29 Improve some comments in ST25R3911B header
2023-05-29 Reformat file
2023-05-29 Set up clang format and reformat some files according to it
2023-05-29 Some fixes to the initialization order
2023-07-04 Add custom Kicad library and nRF52833 symbol
2023-07-04 Add 32.768kHz and 32Mhz crystals to symbol library
2023-07-04 Move nRF52833 pins around on the schematic to better match real locations
2023-07-04 Add series resistor
2023-07-04 Add INA226
2023-07-06 Temporarily disable use of 32.768kHz crystal on Firefly board
    Derive corresponding clock from high-frequency oscillator instead.
2023-07-07 Switch most capacitors to LCSC basic parts instead of extended ones.
2023-07-07 Revert "Temporarily disable use of 32.768kHz crystal on Firefly board"
    This reverts commit 99171ffd5264699f5d0e75d6aec4b96f300cbca9.
2023-07-12 Add most of the components. Some TODOs still remain.
2023-07-13 Add bunch of NC markers and move one wire a bit
2023-07-15 Draft routing done
2023-07-15 Fix most of DRC violation
2023-07-18 Add an actual USB plug
2023-07-19 Document easyeda2kicad usage
2023-07-21 Add and route debugging connectors
2023-07-21 Add a protection diode
2023-07-21 Add switch and LED
2023-08-03 Start working on power meter firmware
2023-08-03 Reformat a file
2023-08-05 Set up INA226 averaging
2023-08-28 Add a bunch of IDEA configs
2023-11-02 Use BT_UUID_128_ENCODE macro
2023-11-02 Bump Zephyr RTOS version to 3.3.0
2023-11-02 Disable a warning (should go away in the next Zephyr version)
2023-11-03 Migrate to Nordics's ncs 2.5.0 / Zephyr RTOS 3.4.99 (from the Nordic fork) / pigweed from HEAD
2023-11-03 Drop locket support, firmware doesn't fit into RAM anymore
2023-11-03 Revert "Skip one of the firmwares during build"
    This reverts commit 481e5cc1ee18415d0af0016a80cddde4e956c88d.
2023-11-04 Adjust some vscode settings for intellisense to work (slightly) better
2023-11-04 Fix bunch of warnings
    (mostly about things being deprecated in the newer Zephyr RTOS versions)
2023-11-04 Fix build
2023-11-11 Move all firmware-related code to subfolder
2023-11-11 Refactor Voltcraft interaction code into client library and usage example
2023-11-12 Remove deprecating configuration option
2023-11-19 Fix documentation issue
2024-03-10 Try to fix port assignments on Raspberry runner
2024-03-28 Move Ostranna symbol library to a common folder to be able to re-use it in the other projects
2024-03-29 Create a schematic for HITL / debugging board
2024-04-07 Enable UART logging for power meter
2024-04-07 Fix power_meter CMakeLists
2024-04-07 Set CONFIG_SERIAL for power_meter
2024-04-28 Temporarily pin pigweed version to an older commit
    pw_thread_zephyr is broken at HEAD.
2024-05-04 Explicitly enable gpiote in device tree
    Seems to be required in the newer Zephyr versions
2024-08-08 Simplify Thread constructor calls using pw::Function
2024-08-08 Bumpt nrf sdk version
2024-08-08 Don't use the standard ina226 driver, we are doing everything on our own
2024-08-09 Update include to a non-deprecated one
2024-08-20 Revert "Disable buzzer for now"
    This reverts commit 18dd633320dc4b25a6a81094dac3cc944a24d6a7.
2024-08-25 Use /dev/serial/by-id device identifiers to guarantee that correct device is being used
2024-08-28 Add documentation on potential CLion usage for development
2024-09-25 Disable RPC server in lock test for now
2024-10-27 Set up a new Cordyceps board using power meter as a template
    Things to do:
    - Add a header for the Rothult connection
    - Add bunch of vias to better connect ground planes
    - (Optionally) Add more headers for e.g. SPI or I2C support
    - Fix easyeda2kicad library
2024-10-27 Add some stitching vias near the antenna
2024-10-27 Remove some redundant tracks
2024-10-28 Add required connectors
2024-10-28 Cordyceps board sent to production
    Order link: https://jlcpcb.com/user-center/orderDetails/?batchNum=W202410281030321
2024-10-29 Work in progress on esphome-nfc board
    * Done power and clock circuit for PN7160
    * Drafted the board dimensions
2024-10-31 Add information about output path for easyeda2kicad
2024-10-31 Route MCU <--> NFC chip connections
2024-11-01 Re-route D+/D- using differential pair tools
2024-11-03 Clean up symbol libraries
    * Reposition property labels to make them readable
    * Update LCSC references for some parts to use Basic components
    * Provide Basic/Extended property
2024-11-04 esphome-nfc: route & finalize everything except for NFC antenna and corresponding matching circuit
2024-11-05 esphome-nfc final touches
    * Add an antenna and corresponding matching circuitry
    * Add a button (you never know...)
    * Mark components I plan to solder manually as "Do Not Place"
2024-11-06 Add a replacement NFC antenna for the Rothult
2024-11-06 Bump the capacitance of capacitors near the oscillator based on some reading
2024-11-08 Work in progress on the custom black magic probe
    Most of schematic is done, there are some TODOs left.
2024-11-08 Finish with the blackmagic schematic
    Now it's layout/routing time!
2024-11-09 Use easyeda blueprint for USBLC6-2P6 to fix the rotation
2024-11-10 Update the documentation to account for the new python weirdness with global package installations
2024-11-12 Remove unused include
2024-11-12 Improve gitignore to ignore more temporary crap
2024-11-13 Add very basic UART output (O/C) based on the characteristic write
2024-11-13 Slightly rework cordyceps firmware - let the open/close characteristic have "is_closed" semantic
2024-11-17 Fix the small fuckup with the UART RX/TX on cordyceps board
    Oops, I did it again!
    Luckily, we can just reassign those as nRF chips allow to use any pin as RX/TX.
